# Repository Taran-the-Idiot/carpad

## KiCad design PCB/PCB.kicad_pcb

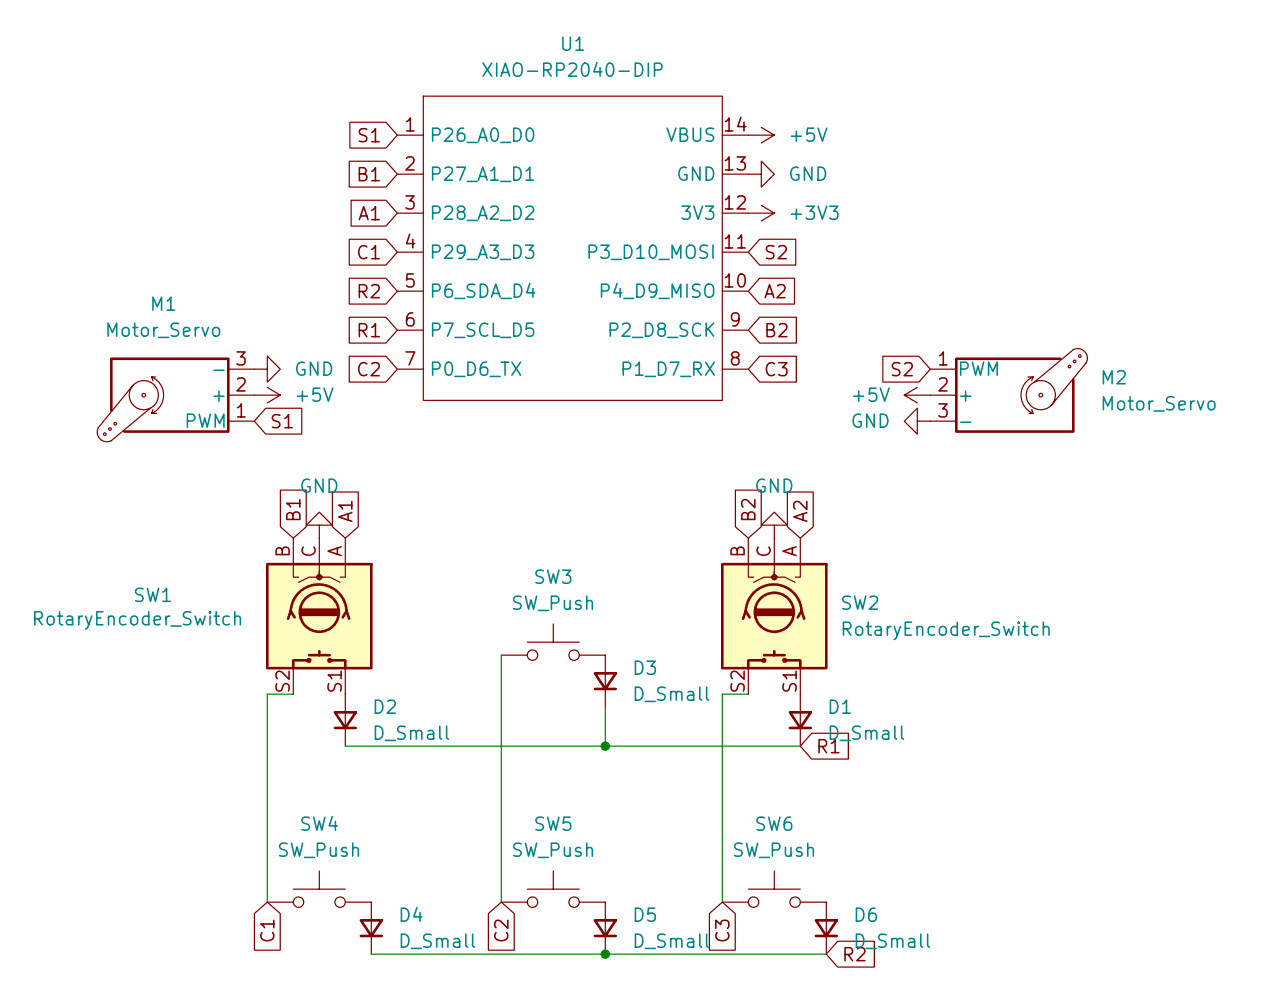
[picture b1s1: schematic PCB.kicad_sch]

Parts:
D1, D2, D3, D4, D5, D6: D_Small; D_DO-35_SOD27_P7.62mm_Horizontal
M1, M2: Motor_Servo; PinSocket_1x03_P2.54mm_Vertical
SW1, SW2: RotaryEncoder_Switch; RotaryEncoder_Alps_EC11E-Switch_Vertical_H20mm
SW3, SW4, SW5, SW6: SW_Push; SW_Cherry_MX_1.00u_PCB
U1: XIAO-RP2040-DIP

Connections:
+3V3: U1.12 (3V3)
+5V: M1.2 (+), M2.2 (+), U1.14 (VBUS)
A1: SW1.A, U1.3 (P28_A2_D2)
A2: SW2.A, U1.10 (P4_D9_MISO)
B1: SW1.B, U1.2 (P27_A1_D1)
B2: SW2.B, U1.9 (P2_D8_SCK)
C1: SW1.S2, SW4.1, U1.4 (P29_A3_D3)
C2: SW3.1, SW5.1, U1.7 (P0_D6_TX)
C3: SW2.S2, SW6.1, U1.8 (P1_D7_RX)
GND: M1.3 (-), M2.3 (-), SW1.C, SW2.C, U1.13 (GND)
unnamed: D1.2 (A), SW2.S1
unnamed: D2.2 (A), SW1.S1
unnamed: D3.2 (A), SW3.2
unnamed: D4.2 (A), SW4.2
unnamed: D5.2 (A), SW5.2
unnamed: D6.2 (A), SW6.2
R1: D1.1 (K), D2.1 (K), D3.1 (K), U1.6 (P7_SCL_D5)
R2: D4.1 (K), D5.1 (K), D6.1 (K), U1.5 (P6_SDA_D4)
S1: M1.1 (PWM), U1.1 (P26_A0_D0)
S2: M2.1 (PWM), U1.11 (P3_D10_MOSI)

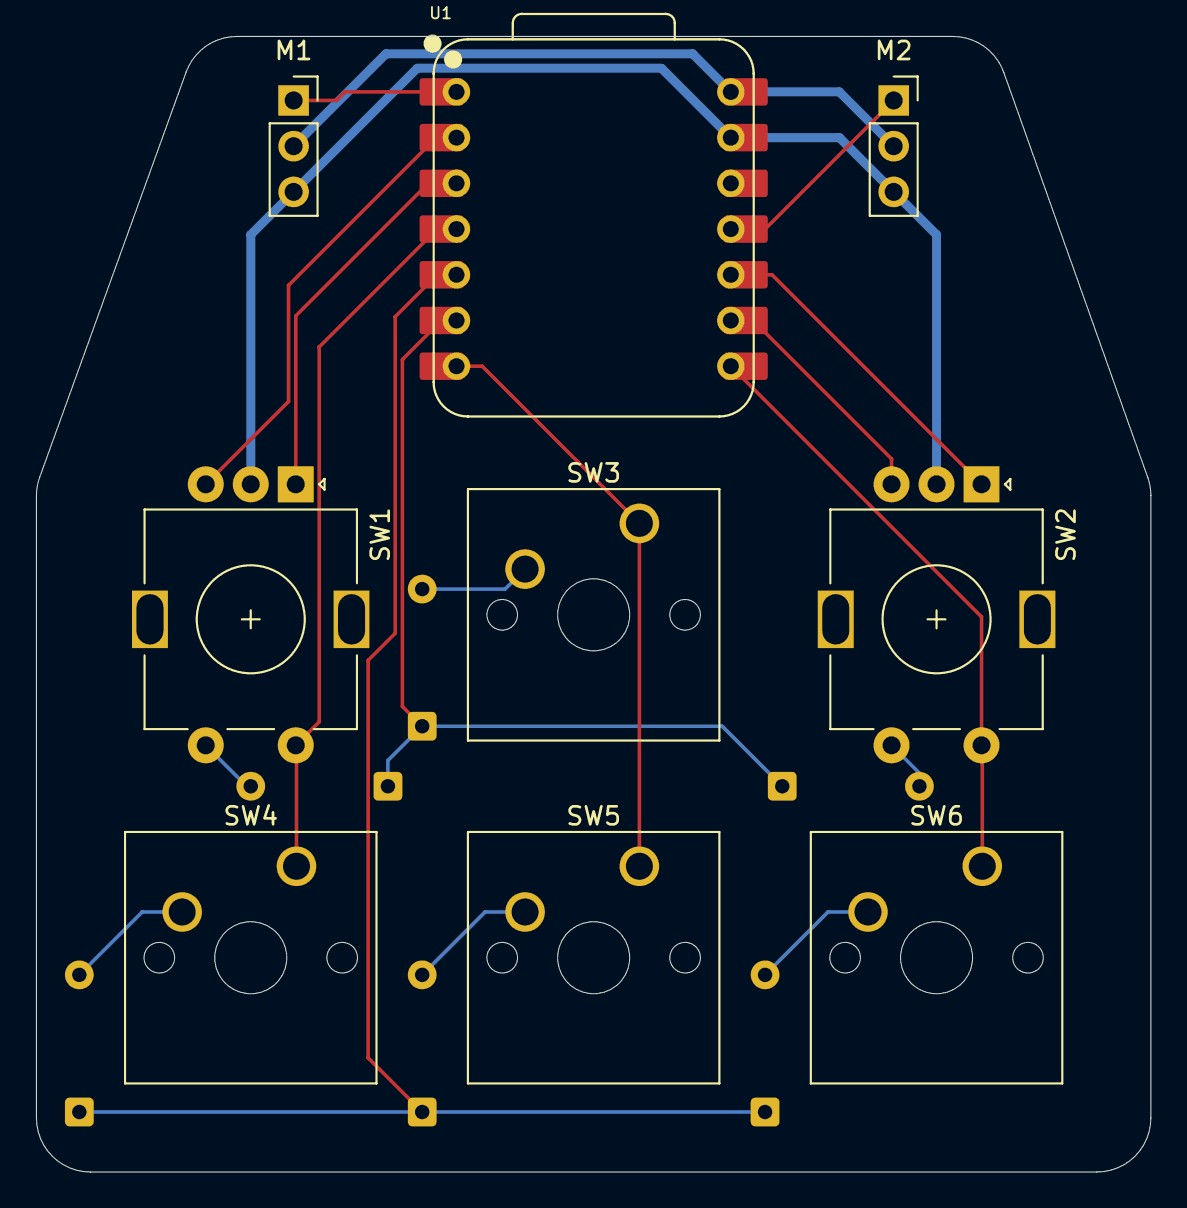
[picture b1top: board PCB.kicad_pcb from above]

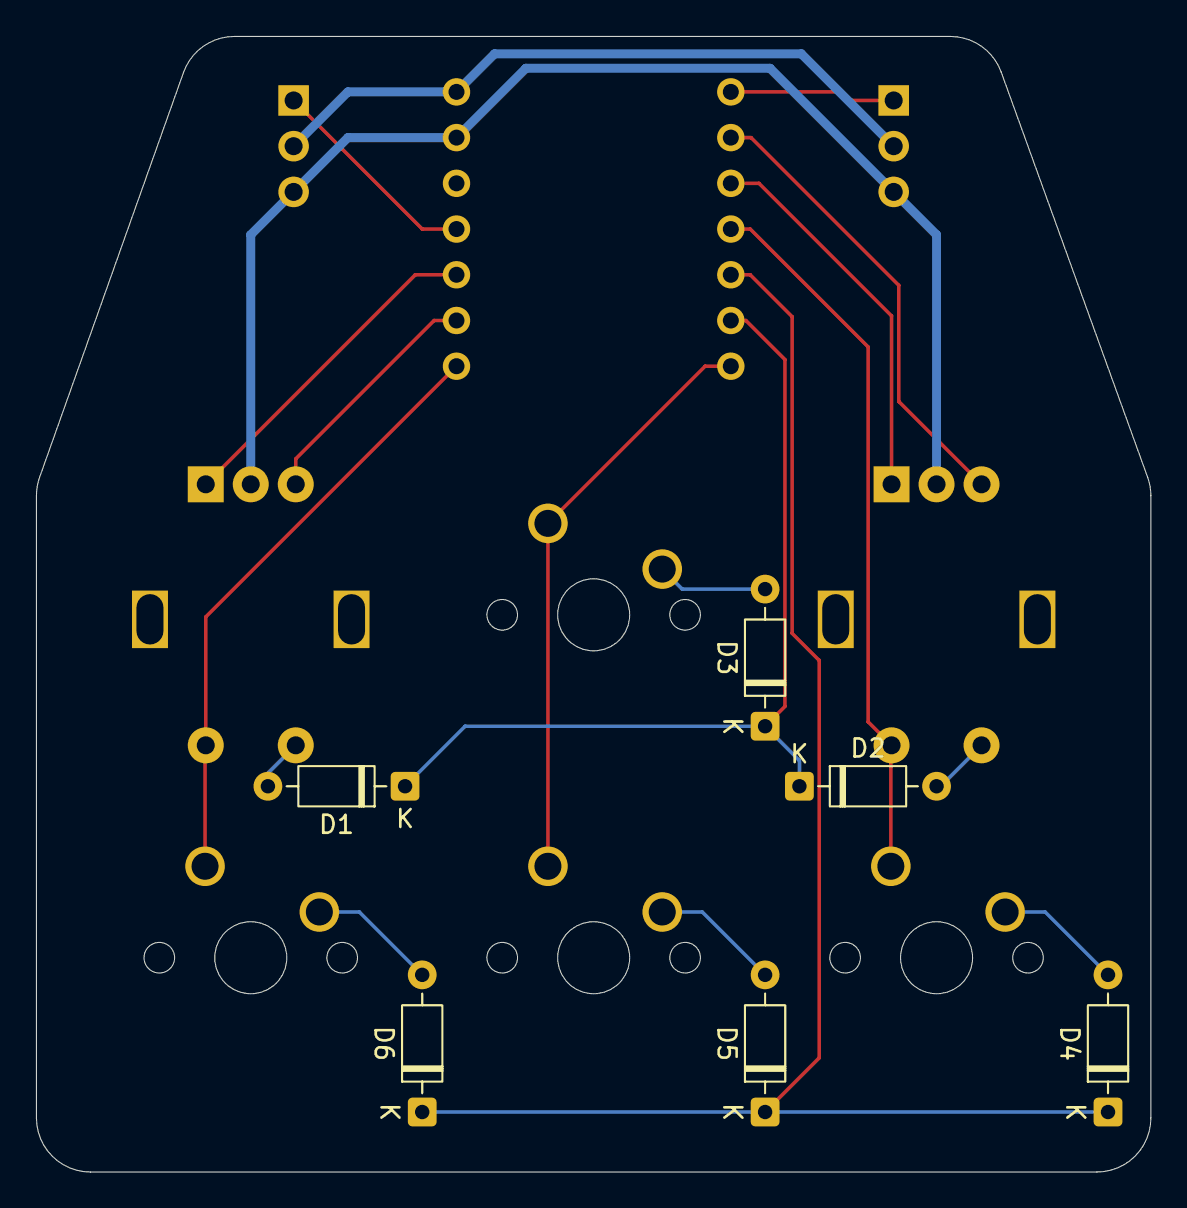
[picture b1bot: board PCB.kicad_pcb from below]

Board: 2 copper layers, 61.9 x 63.1 mm, 15 parts (6 on the bottom side), 19 nets.

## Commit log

2026-05-02 potato
2026-05-02 bleh
